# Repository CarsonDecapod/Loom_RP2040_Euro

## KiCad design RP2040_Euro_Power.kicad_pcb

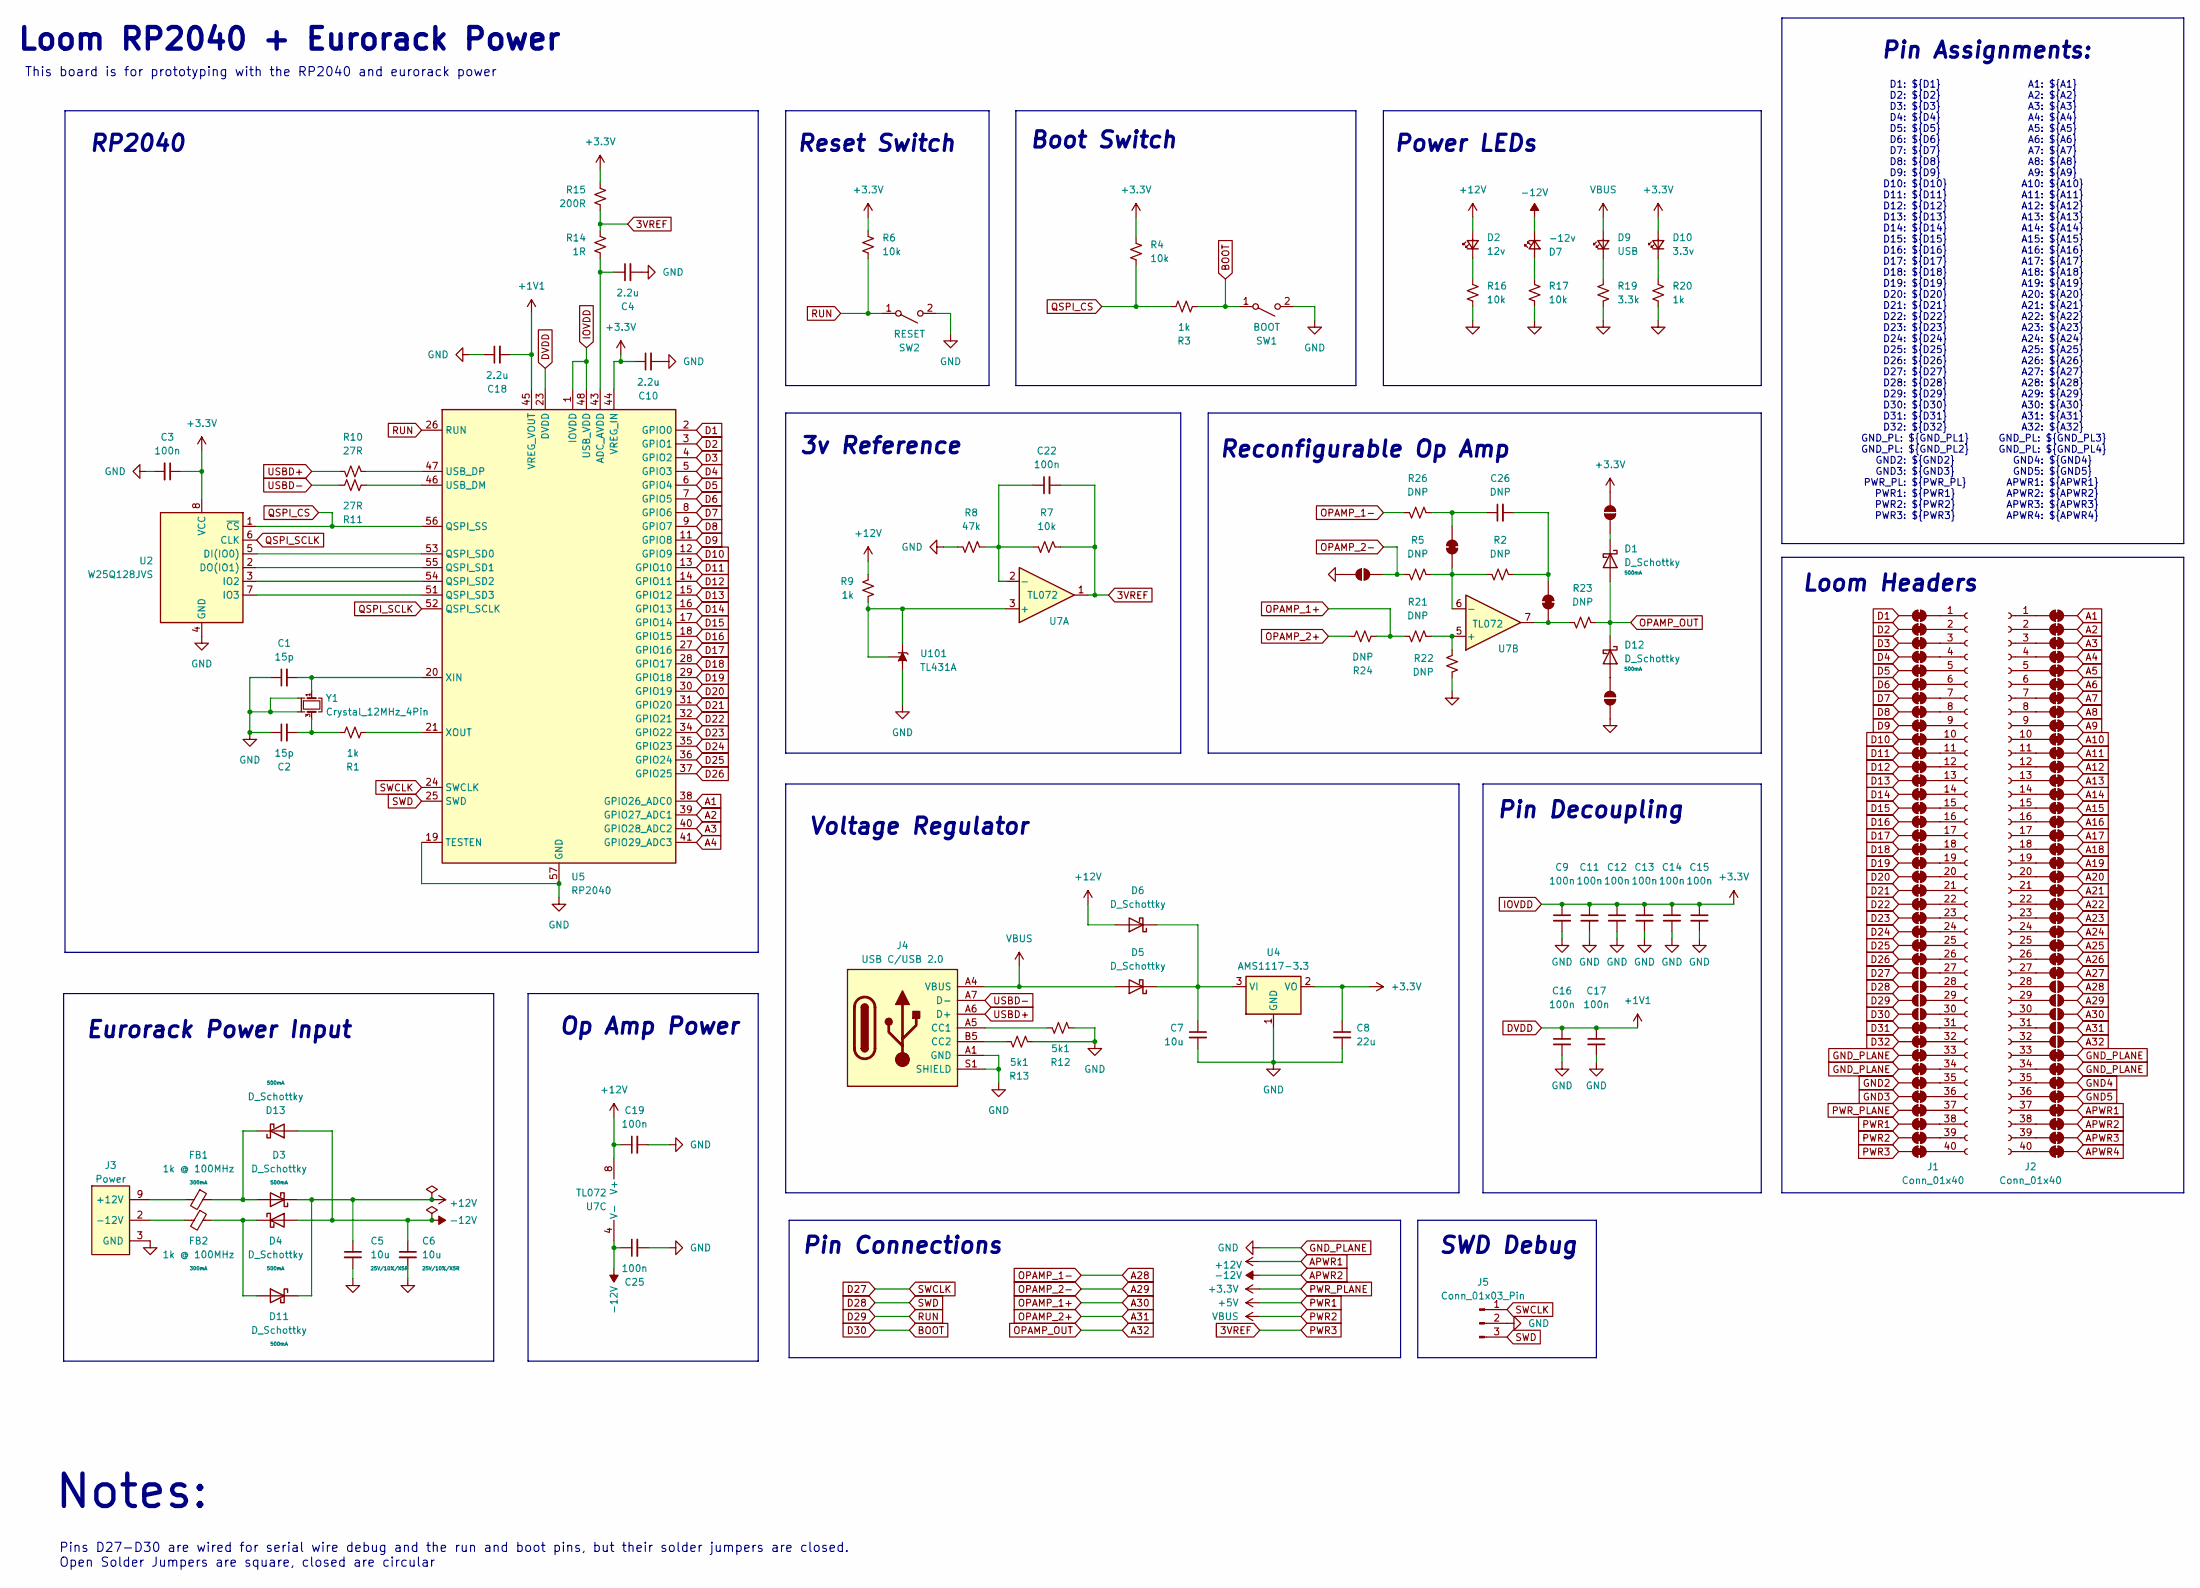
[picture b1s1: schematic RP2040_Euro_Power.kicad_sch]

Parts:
C1, C2: 15p; C_0603_HandSolder; Rating 25V/10%/C0G; MPN CL10C150JB8NNNC; LCSC C1644
C3, C9, C11, C12, C13, C14, C15, C16, C17, C19, C22, C25: 100n; C_0603_HandSolder; Rating 25V/10%/C0G; MPN CC0603KRX7R9BB104; LCSC C14663
C4, C10, C18: 2.2u; C_0603_HandSolder; Rating 25V/10%/C0G; MPN CL10A225KO8NNNC; LCSC C23630
C5, C6: 10u; C_0805_HandSolder; Rating 25V/10%/X5R; MPN CL21A106KAYNNNE; DigiKey 490-16824-1-ND
C7: 10u; C_0805_HandSolder; Rating 25V/10%/C0G; MPN CL21A106KAYNNNE; LCSC C15850
C8: 22u; C_0805_HandSolder; Rating 25V/10%/C0G; MPN CL21A226MAQNNNE; LCSC C45783
C26: DNP; C_0603_HandSolder; Rating 25V/10%; mpn C1608X7R1E104K080AA
D1, D3, D4, D11, D12, D13: D_Schottky; D_SMA; Rating 500mA; MPN SS14; DigiKey 1727-3876-1-ND
D2: 12v; LED_0805_2012Metric; MPN KT-0805G; LCSC C2297
D5, D6: D_Schottky; D_SMA; MPN SS14; LCSC C2480
D7: -12v; LED_0805_2012Metric; MPN KT-0805G; LCSC C2297
D9: USB; LED_0805_2012Metric; MPN KT-0805G; LCSC C2297
D10: 3.3v; LED_0805_2012Metric; MPN KT-0805G; LCSC C2297
FB1, FB2: 1k @ 100MHz; L_0603_HandSolder; Rating 300mA; MPN GZ1608D601TF; DigiKey 490-5212-1-ND
J1, J2: Conn_01x40; PinHeader_1x40_P2.54mm_Vertical
J3: Power; Eurorack_Power_2x5_Shrouded_Lock_LongPads; MPN 302-S101
J4: USB C/USB 2.0; USB_C_Receptacle_GCT_USB4105-xx-A_16P_TopMnt_Horizontal; MPN TYPE-C 16PIN 2MD(073); LCSC C2765186
J5: Conn_01x03_Pin; PinHeader_1x03_P2.54mm_Vertical
JP1, JP201: Jumper_Closed; SolderJumper-2_P1.3mm_Bridged_RoundedPad1.0x1.5mm
JP2, JP3, JP4, JP127, JP128, JP129, JP130, JP168, JP169, JP170, JP171, JP172: SolderJumper_2_Open; SolderJumper-2_P1.3mm_Open_Pad1.0x1.5mm
JP101, JP102, JP103, JP104, JP105, JP106, JP107, JP108, JP109, JP110, JP111, JP112, JP113, JP114, JP115, JP116, JP117, JP118, JP119, JP120, JP121, JP122, JP123, JP124, JP125, JP126, JP131, JP132, JP133, JP134, JP135, JP136, JP137, JP138, JP139, JP140, JP141, JP142, JP143, JP144, JP145, JP146, JP147, JP148, JP149, JP150, JP151, JP152, JP153, JP154, JP155, JP156, JP157, JP158, JP159, JP160, JP161, JP162, JP163, JP164, JP165, JP166, JP167, JP173, JP174, JP175, JP176, JP177, JP178, JP179, JP180: SolderJumper-2_P1.3mm_Bridged_RoundedPad1.0x1.5mm
R1, R3, R9, R20: 1k; R_0603_HandSolder; Rating 100mW/1%/Thin; MPN 0603WAF1001T5E; LCSC C21190
R2, R5, R21, R22, R23, R24, R26: DNP; R_0603_HandSolder; Rating 100mW/1%/Thin
R4, R6, R7, R16, R17: 10k; R_0603_HandSolder; Rating 100mW/1%/Thin; MPN 0603WAF1002T5E; LCSC C25804
R8: 47k; R_0603_HandSolder; Rating 100mW/1%/Thin; MPN 0603WAF4702T5E; LCSC C25819
R10, R11: 27R; R_0603_HandSolder; Rating 100mW/1%/Thin; MPN 0603WAF270JT5E; LCSC C25190
R12, R13: 5k1; R_0603_HandSolder; Rating 100mW/1%/Thin; MPN 0603WAF5101T5E; LCSC C23186
R14: 1R; R_0603_HandSolder; Rating 100mW/1%/Thin; MPN 0603WAF100KT5E; LCSC C22936
R15: 200R; R_0603_HandSolder; Rating 100mW/1%/Thin; MPN 0603WAF2000T5E; LCSC C8218
R19: 3.3k; R_0603_HandSolder; Rating 100mW/1%/Thin; MPN 0603WAF3301T5E; LCSC C22978
SW1: BOOT; SW-SMD_TS24CA; MPN TS24CA; LCSC C393942
SW2: RESET; SW-SMD_TS24CA; MPN TS24CA; LCSC C393942
U2: W25Q128JVS; SOIC-8_5.23x5.23mm_P1.27mm; MPN W25Q128JVSIQ; LCSC C97521
U4: AMS1117-3.3; SOT-223-3_TabPin2; MPN AMS1117-3.3; LCSC C6186
U5: RP2040; QFN-56-1EP_7x7mm_P0.4mm_EP3.2x3.2mm; MPN RP2040; LCSC C2040
U7: TL072; SOIC-8_3.9x4.9mm_P1.27mm; MPN TL072CDT; LCSC C6961
U101: TL431A; SOT-23; Rating 1%; MPN TL431BSA-7, TL431AQDBZR,215;; DigiKey 1727-4260-1-ND
Y1: Crystal_12MHz_4Pin; Crystal_SMD_Abracon_ABM8G-4Pin_3.2x2.5mm; MPN ABM8-272-T3; LCSC C20625731

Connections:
3VREF: C22.2, JP140.2 (B), R7.2, R14.1, R15.2, U7.1
A1: JP141.1 (A), U5.38 (GPIO26_ADC0)
A2: JP142.1 (A), U5.39 (GPIO27_ADC1)
A3: JP143.1 (A), U5.40 (GPIO28_ADC2)
A4: JP144.1 (A), U5.41 (GPIO29_ADC3)
A5: JP145.1 (A)
A6: JP146.1 (A)
A7: JP147.1 (A)
A8: JP148.1 (A)
A9: JP149.1 (A)
A10: JP150.1 (A)
A11: JP151.1 (A)
A12: JP152.1 (A)
A13: JP153.1 (A)
A14: JP154.1 (A)
A15: JP155.1 (A)
A16: JP156.1 (A)
A17: JP157.1 (A)
A18: JP158.1 (A)
A19: JP159.1 (A)
A20: JP160.1 (A)
A21: JP161.1 (A)
A22: JP162.1 (A)
A23: JP163.1 (A)
A24: JP164.1 (A)
A25: JP165.1 (A)
A26: JP166.1 (A)
A27: JP167.1 (A)
A28: JP168.2 (B), R26.1
A29: JP2.2 (B), JP169.2 (B), R5.1
A30: JP170.2 (B), R21.1, R24.2
A31: JP171.2 (B), R24.1
A32: D1.2 (A), D12.1 (K), JP172.2 (B), R23.2
APWR1: C5.1, C19.1, D2.2 (A), D3.1 (K), D6.2 (A), D11.1 (K), JP177.1 (A), R9.1, U7.8 (V+)
APWR2: C6.1, C25.1, D4.2 (A), D7.1 (K), D13.2 (A), JP178.1 (A), U7.4 (V-)
APWR3: JP179.1 (A)
APWR4: JP180.1 (A)
BOOT: JP130.1 (A), R3.2, SW1.1 (A)
D1: JP101.2 (B), U5.2 (GPIO0)
D2: JP102.2 (B), U5.3 (GPIO1)
D3: JP103.2 (B), U5.4 (GPIO2)
D4: JP104.2 (B), U5.5 (GPIO3)
D5: JP105.2 (B), U5.6 (GPIO4)
D6: JP106.2 (B), U5.7 (GPIO5)
D7: JP107.2 (B), U5.8 (GPIO6)
D8: JP108.2 (B), U5.9 (GPIO7)
D9: JP109.2 (B), U5.11 (GPIO8)
D10: JP110.2 (B), U5.12 (GPIO9)
D11: JP111.2 (B), U5.13 (GPIO10)
D12: JP112.2 (B), U5.14 (GPIO11)
D13: JP113.2 (B), U5.15 (GPIO12)
D14: JP114.2 (B), U5.16 (GPIO13)
D15: JP115.2 (B), U5.17 (GPIO14)
D16: JP116.2 (B), U5.18 (GPIO15)
D17: JP117.2 (B), U5.27 (GPIO16)
D18: JP118.2 (B), U5.28 (GPIO17)
D19: JP119.2 (B), U5.29 (GPIO18)
D20: JP120.2 (B), U5.30 (GPIO19)
D21: JP121.2 (B), U5.31 (GPIO20)
D22: JP122.2 (B), U5.32 (GPIO21)
D23: JP123.2 (B), U5.34 (GPIO22)
D24: JP124.2 (B), U5.35 (GPIO23)
D25: JP125.2 (B), U5.36 (GPIO24)
D26: JP126.2 (B), U5.37 (GPIO25)
D27: J5.1, JP127.1 (A), U5.24 (SWCLK)
D28: J5.3, JP128.1 (A), U5.25 (SWD)
D29: JP129.1 (A), R6.1, SW2.1 (A), U5.26 (RUN)
D31: JP131.2 (B)
D32: JP132.2 (B)
DVDD: C16.1, C17.1, C18.2, U5.23 (DVDD), U5.45 (VREG_VOUT), U5.50 (DVDD)
GND2: JP135.2 (B)
GND3: JP136.2 (B)
GND4: JP175.1 (A)
GND5: JP176.1 (A)
GND_PLANE: C1.1, C2.1, C3.2, C4.2, C5.2, C6.2, C7.2, C8.2, C9.2, C10.2, C11.2, C12.2, C13.2, C14.2, C15.2, C16.2, C17.2, C18.1, C19.2, C25.2, J3.3 (GND), J3.4 (GND), J3.5 (GND), J3.6 (GND), J3.7 (GND), J3.8 (GND), J4.A1 (GND), J4.A12 (GND), J4.B1 (GND), J4.B12 (GND), J4.S1 (SHIELD), J5.2, JP2.1 (A), JP4.1 (A), JP133.2 (B), JP134.2 (B), JP173.1 (A), JP174.1 (A), R8.1, R12.2, R13.2, R16.1, R17.1, R19.2, R20.2, R22.1, SW1.2 (B), SW2.2 (B), U2.4 (GND), U4.1 (GND), U5.19 (TESTEN), U5.57 (GND), U101.3 (A), Y1.2, Y1.4
IOVDD: C3.1, C8.1, C9.1, C10.1, C11.1, C12.1, C13.1, C14.1, C15.1, D10.2 (A), JP3.2 (B), JP137.2 (B), R4.2, R6.2, R15.1, U2.8 (VCC), U4.2 (VO), U5.1 (IOVDD), U5.10 (IOVDD), U5.22 (IOVDD), U5.33 (IOVDD), U5.42 (IOVDD), U5.44 (VREG_IN), U5.48 (USB_VDD), U5.49 (IOVDD)
unnamed: C2.2, R1.1, Y1.3
unnamed: D1.1 (K), JP3.1 (A)
unnamed: D2.1 (K), R16.2
unnamed: C7.1, D5.1 (K), D6.1 (K), U4.3 (VI)
unnamed: D7.2 (A), R17.2
unnamed: D9.1 (K), R19.1
unnamed: D10.1 (K), R20.1
unnamed: D4.1 (K), D11.2 (A), FB2.1
unnamed: D12.2 (A), JP4.2 (B)
unnamed: D3.2 (A), D13.1 (K), FB1.1
unnamed: FB1.2, J3.9 (+12V), J3.10 (+12V)
unnamed: FB2.2, J3.1 (-12V), J3.2 (-12V)
unnamed: J1.1, JP101.1 (A)
unnamed: J1.2, JP102.1 (A)
unnamed: J1.3, JP103.1 (A)
unnamed: J1.4, JP104.1 (A)
unnamed: J1.5, JP105.1 (A)
unnamed: J1.6, JP106.1 (A)
unnamed: J1.7, JP107.1 (A)
unnamed: J1.8, JP108.1 (A)
unnamed: J1.9, JP109.1 (A)
unnamed: J1.10, JP110.1 (A)
unnamed: J1.11, JP111.1 (A)
unnamed: J1.12, JP112.1 (A)
unnamed: J1.13, JP113.1 (A)
unnamed: J1.14, JP114.1 (A)
unnamed: J1.15, JP115.1 (A)
unnamed: J1.16, JP116.1 (A)
unnamed: J1.17, JP117.1 (A)
unnamed: J1.18, JP118.1 (A)
unnamed: J1.19, JP119.1 (A)
unnamed: J1.20, JP120.1 (A)
unnamed: J1.21, JP121.1 (A)
unnamed: J1.22, JP122.1 (A)
unnamed: J1.23, JP123.1 (A)
unnamed: J1.24, JP124.1 (A)
unnamed: J1.25, JP125.1 (A)
unnamed: J1.26, JP126.1 (A)
unnamed: J1.27, JP127.2 (B)
unnamed: J1.28, JP128.2 (B)
unnamed: J1.29, JP129.2 (B)
unnamed: J1.30, JP130.2 (B)
unnamed: J1.31, JP131.1 (A)
unnamed: J1.32, JP132.1 (A)
unnamed: J1.33, JP133.1 (A)
unnamed: J1.34, JP134.1 (A)
unnamed: J1.35, JP135.1 (A)
unnamed: J1.36, JP136.1 (A)
unnamed: J1.37, JP137.1 (A)
unnamed: J1.38, JP138.1 (A)
unnamed: J1.39, JP139.1 (A)
unnamed: J1.40, JP140.1 (A)
unnamed: J2.1, JP141.2 (B)
unnamed: J2.2, JP142.2 (B)
unnamed: J2.3, JP143.2 (B)
unnamed: J2.4, JP144.2 (B)
unnamed: J2.5, JP145.2 (B)
unnamed: J2.6, JP146.2 (B)
unnamed: J2.7, JP147.2 (B)
unnamed: J2.8, JP148.2 (B)
unnamed: J2.9, JP149.2 (B)
unnamed: J2.10, JP150.2 (B)
unnamed: J2.11, JP151.2 (B)
unnamed: J2.12, JP152.2 (B)
unnamed: J2.13, JP153.2 (B)
unnamed: J2.14, JP154.2 (B)
unnamed: J2.15, JP155.2 (B)
unnamed: J2.16, JP156.2 (B)
unnamed: J2.17, JP157.2 (B)
unnamed: J2.18, JP158.2 (B)
unnamed: J2.19, JP159.2 (B)
unnamed: J2.20, JP160.2 (B)
unnamed: J2.21, JP161.2 (B)
unnamed: J2.22, JP162.2 (B)
unnamed: J2.23, JP163.2 (B)
unnamed: J2.24, JP164.2 (B)
unnamed: J2.25, JP165.2 (B)
unnamed: J2.26, JP166.2 (B)
unnamed: J2.27, JP167.2 (B)
unnamed: J2.28, JP168.1 (A)
unnamed: J2.29, JP169.1 (A)
unnamed: J2.30, JP170.1 (A)
unnamed: J2.31, JP171.1 (A)
unnamed: J2.32, JP172.1 (A)
unnamed: J2.33, JP173.2 (B)
unnamed: J2.34, JP174.2 (B)
unnamed: J2.35, JP175.2 (B)
unnamed: J2.36, JP176.2 (B)
unnamed: J2.37, JP177.2 (B)
unnamed: J2.38, JP178.2 (B)
unnamed: J2.39, JP179.2 (B)
unnamed: J2.40, JP180.2 (B)
unnamed: J4.A5 (CC1), R12.1
unnamed: J4.B5 (CC2), R13.1
unnamed: JP1.1 (A), R2.1, R5.2, U7.6 (-)
unnamed: C26.1, JP1.2 (B), R26.2
unnamed: JP201.1 (A), R23.1, U7.7
unnamed: C26.2, JP201.2 (B), R2.2
unnamed: U2.5 (DI(IO0)), U5.53 (QSPI_SD0)
unnamed: U2.2 (DO(IO1)), U5.55 (QSPI_SD1)
unnamed: U2.3 (IO2), U5.54 (QSPI_SD2)
unnamed: U2.7 (IO3), U5.51 (QSPI_SD3)
unnamed: C4.1, R14.2, U5.43 (ADC_AVDD)
unnamed: R11.1, U5.46 (USB_DM)
unnamed: R10.1, U5.47 (USB_DP)
unnamed: C1.2, U5.20 (XIN), Y1.1
unnamed: R1.2, U5.21 (XOUT)
unnamed: C22.1, R7.1, R8.2, U7.2 (-)
unnamed: R21.2, R22.2, U7.5 (+)
unnamed: R9.2, U7.3 (+), U101.1 (K), U101.2 (REF)
PWR1: JP138.2 (B)
PWR2: D5.2 (A), D9.2 (A), J4.A4 (VBUS), J4.A9 (VBUS), J4.B4 (VBUS), J4.B9 (VBUS), JP139.2 (B)
QSPI_CS: R3.1, R4.1, U2.1 (~CS), U5.56 (QSPI_SS)
QSPI_SCLK: U2.6 (CLK), U5.52 (QSPI_SCLK)
USBD+: J4.A6 (D+), J4.B6 (D+), R10.2
USBD-: J4.A7 (D-), J4.B7 (D-), R11.2

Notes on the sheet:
Pin Assignments:
A1: ${A1} A2: ${A2} A3: ${A3} A4: ${A4} A5: ${A5} A6: ${A6} A7: ${A7} A8: ${A8} A9: ${A9} A10: ${A10} A11: ${A11} A12: ${A12} A13: ${A13} A14: ${A14} A15: ${A15} A16: ${A16} A17: ${A17} A18: ${A18} A19: ${A19} A20: ${A20} A21: ${A21} A22: ${A22} A23: ${A23} A24: ${A24} A25: ${A25} A26: ${A26} A27: 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
Loom RP2040 + Eurorack Power
Power LEDs
Notes:
Reconfigurable Op Amp
RP2040
Reset Switch
This board is for prototyping with the RP2040 and eurorack power
D1: ${D1} D2: ${D2} D3: ${D3} D4: ${D4} D5: ${D5} D6: ${D6} D7: ${D7} D8: ${D8} D9: ${D9} D10: ${D10} D11: ${D11} D12: ${D12} D13: ${D13} D14: ${D14} D15: ${D15} D16: ${D16} D17: ${D17} D18: ${D18} D19: ${D19} D20: ${D20} D21: ${D21} D22: ${D22} D23: ${D23} D24: ${D24} D25: ${D25} D26: ${D26} D27: 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
Eurorack Power Input
Pin Decoupling
Voltage Regulator
Loom Headers
SWD Debug
3v Reference
Boot Switch
Op Amp Power
Pins D27-D30 are wired for serial wire debug and the run and boot pins, but their solder jumpers are closed. Open Solder Jumpers are square, closed are circular
Pin Connections

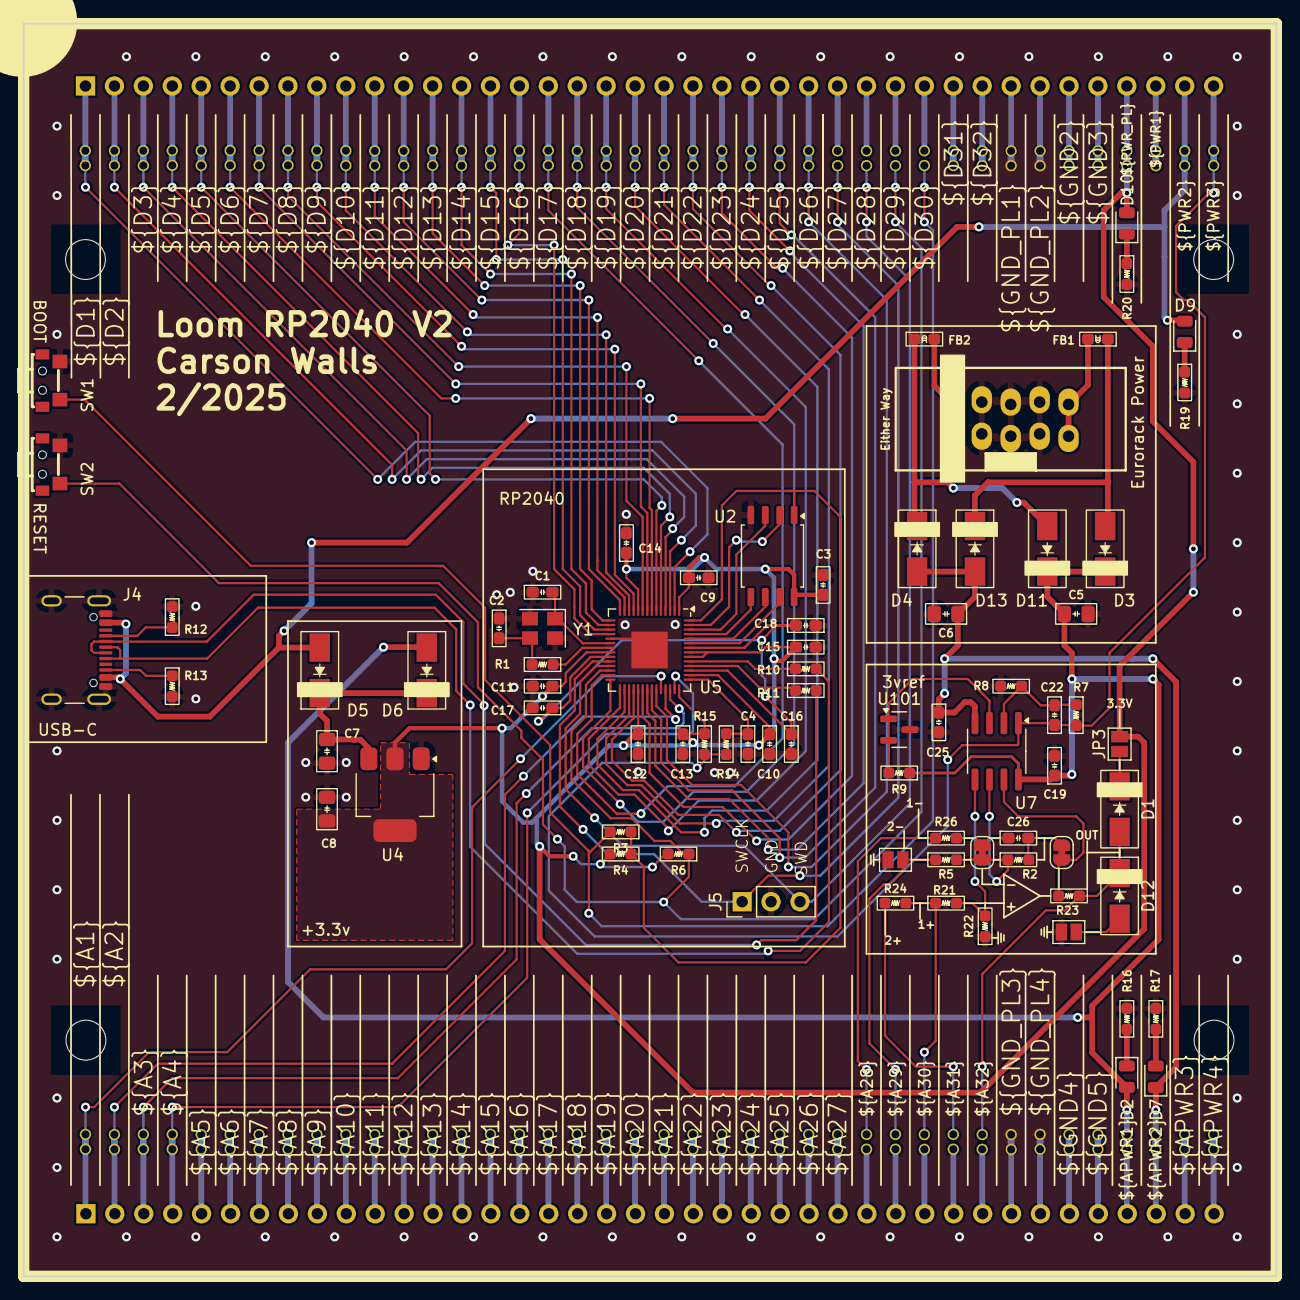
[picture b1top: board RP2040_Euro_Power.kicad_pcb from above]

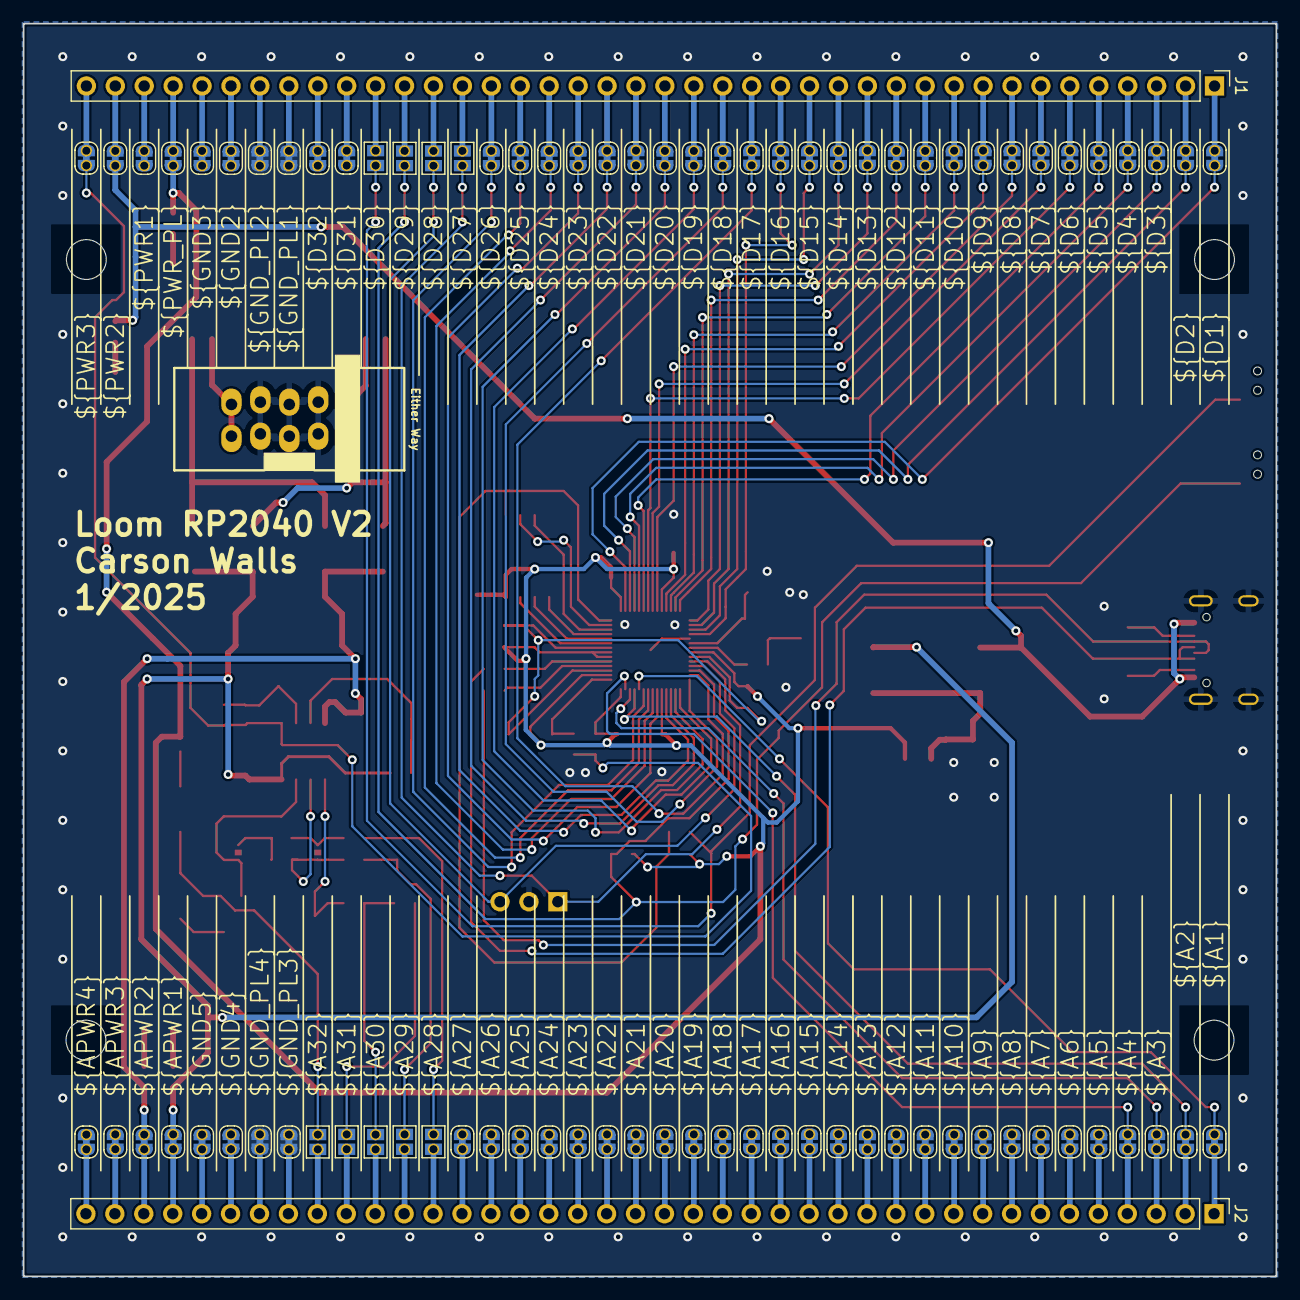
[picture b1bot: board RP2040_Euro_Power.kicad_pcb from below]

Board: 2 copper layers, 110.0 x 110.0 mm, 158 parts (82 on the bottom side), 160 nets.

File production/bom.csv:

Designator,Footprint,Quantity,Value,LCSC Part #
"C1, C2",C_0603_HandSolder,2,15p,C1644
"C10, C18, C4",C_0603_HandSolder,3,2.2u,C23630
"C11, C12, C13, C14, C15, C16, C17, C19, C22, C25, C3, C9",C_0603_HandSolder,12,100n,C14663
"C5, C6, C7",C_0805_HandSolder,3,10u,C15850
C8,C_0805_HandSolder,1,22u,C45783
"D1, D11, D12, D13, D3, D4, D5, D6",D_SMA,8,D_Schottky,C2480
D10,0805,1,3.3v,C2297
D2,0805,1,12v,C2297
D7,0805,1,-12v,C2297
D9,0805,1,USB,C2297
"FB1, FB2",L_0603_HandSolder,2,1k @ 100MHz,C1002
"J1, J2",PinHeader_1x40_P2.54mm_Vertical,2,Conn_01x40,
J3,Eurorack_Power_2x5_Shrouded_Lock_LongPads,1,Power,
J4,USB_C_Receptacle_GCT_USB4105-xx-A_16P_TopMnt_Horizontal,1,USB C/USB 2.0,C2765186 
J5,PinHeader_1x03_P2.54mm_Vertical,1,Conn_01x03_Pin,
"JP1, JP201",SolderJumper-2_P1.3mm_Bridged_RoundedPad1.0x1.5mm,2,Jumper_Closed,
"R1, R20, R3, R9",R_0603_HandSolder,4,1k,C21190
"R10, R11",R_0603_HandSolder,2,27R,C25190
"R12, R13",R_0603_HandSolder,2,5k1,C23186
R14,R_0603_HandSolder,1,1R,C22936
R15,R_0603_HandSolder,1,200R,C8218
"R16, R17, R4, R6, R7",R_0603_HandSolder,5,10k,C25804
R19,R_0603_HandSolder,1,3.3k,C22978
R8,R_0603_HandSolder,1,47k,C25819 
SW1,SW-SMD_TS24CA,1,BOOT,C139797
SW2,SW-SMD_TS24CA,1,RESET,C139797
U101,SOT-23,1,TL431A,C79737
U2,SOIC-8_5.23x5.23mm_P1.27mm,1,W25Q128JVS,C97521
U4,SOT-223-3_TabPin2,1,AMS1117-3.3,C6186
U5,QFN-56-1EP_7x7mm_P0.4mm_EP3.2x3.2mm,1,RP2040,C2040
U7,SOIC-8_3.9x4.9mm_P1.27mm,1,TL072,C6961
Y1,Crystal_SMD_Abracon_ABM8G-4Pin_3.2x2.5mm,1,Crystal_12MHz_4Pin,C20625731

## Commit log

2024-07-04 Schematic ready to start board layout.
2024-07-05 half of the parts placed on board
2024-07-05 all parts placed on board
2024-07-05 Board mostly layed out, ready to start routing
2024-07-06 Second op amp used. Ready for routing
2024-07-07 First draft of routing done. Still need to clean everything up, but it passes DRC.
2024-08-22 Loom RP2040 V1 Ordered
2024-12-30 Moved buttons to the side, disconnected opamp
2025-01-08 RP2040 Updated
    Moved buttons to side, removed 5v LDO
2025-01-10 Version 2 Basically ready to order
2025-02-09 Version 2 ready to order
